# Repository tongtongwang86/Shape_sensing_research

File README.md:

# Capacitive 6DOF Strain Sensor for Soft Robot Shape Reconstruction

This project implements a model-based proprioception system for soft robots using embedded capacitive strain sensors, inspired by the Flex-2P6D sensor design from Feliu-Talegon et al. ("Advancing Soft Robot Proprioception Through 6D Strain Sensors Embedding", Soft Robotics 2025). The approach uses a two-plate capacitive sensor that measures relative displacement and rotation between plates to compute the full 6D strain (twist, bending in two axes, axial stretch, and shear in two axes) at discrete points along the robot body. These strain measurements are then integrated using the Geometric Variable-Strain (GVS) model based on SE(3) Lie group kinematics to reconstruct the complete 3D shape of the soft manipulator. This repository contains the KiCad PCB design files for the sensor board (featuring the AD7147 capacitance-to-digital converter) and a simulation suite that generates synthetic strain data and visualizes the resulting 3D shape reconstruction in MATLAB.

## Initial "Simulation" Results

## PCB Design

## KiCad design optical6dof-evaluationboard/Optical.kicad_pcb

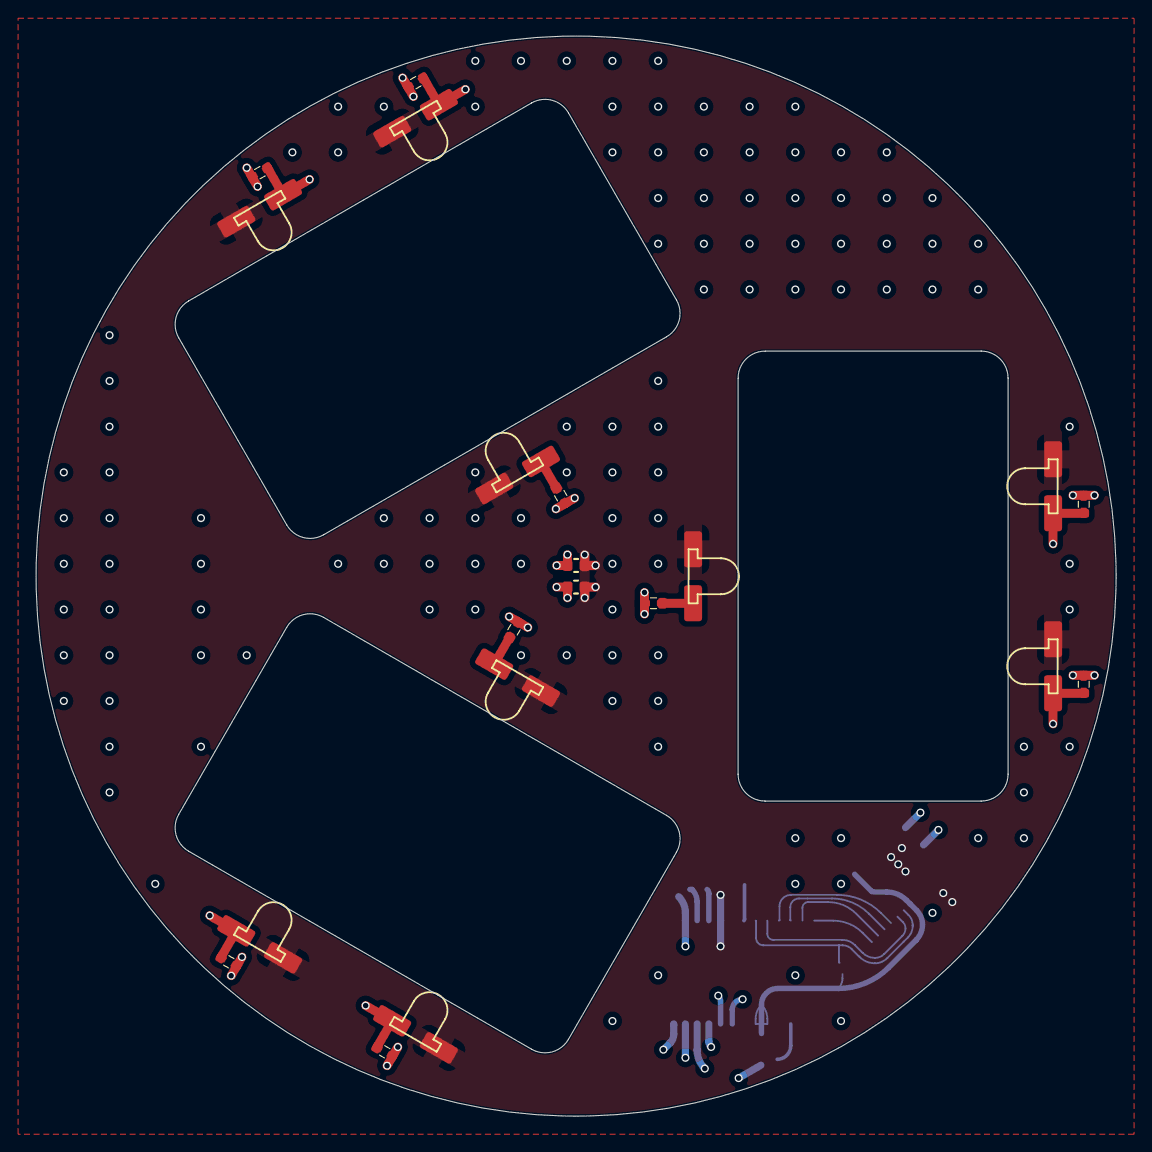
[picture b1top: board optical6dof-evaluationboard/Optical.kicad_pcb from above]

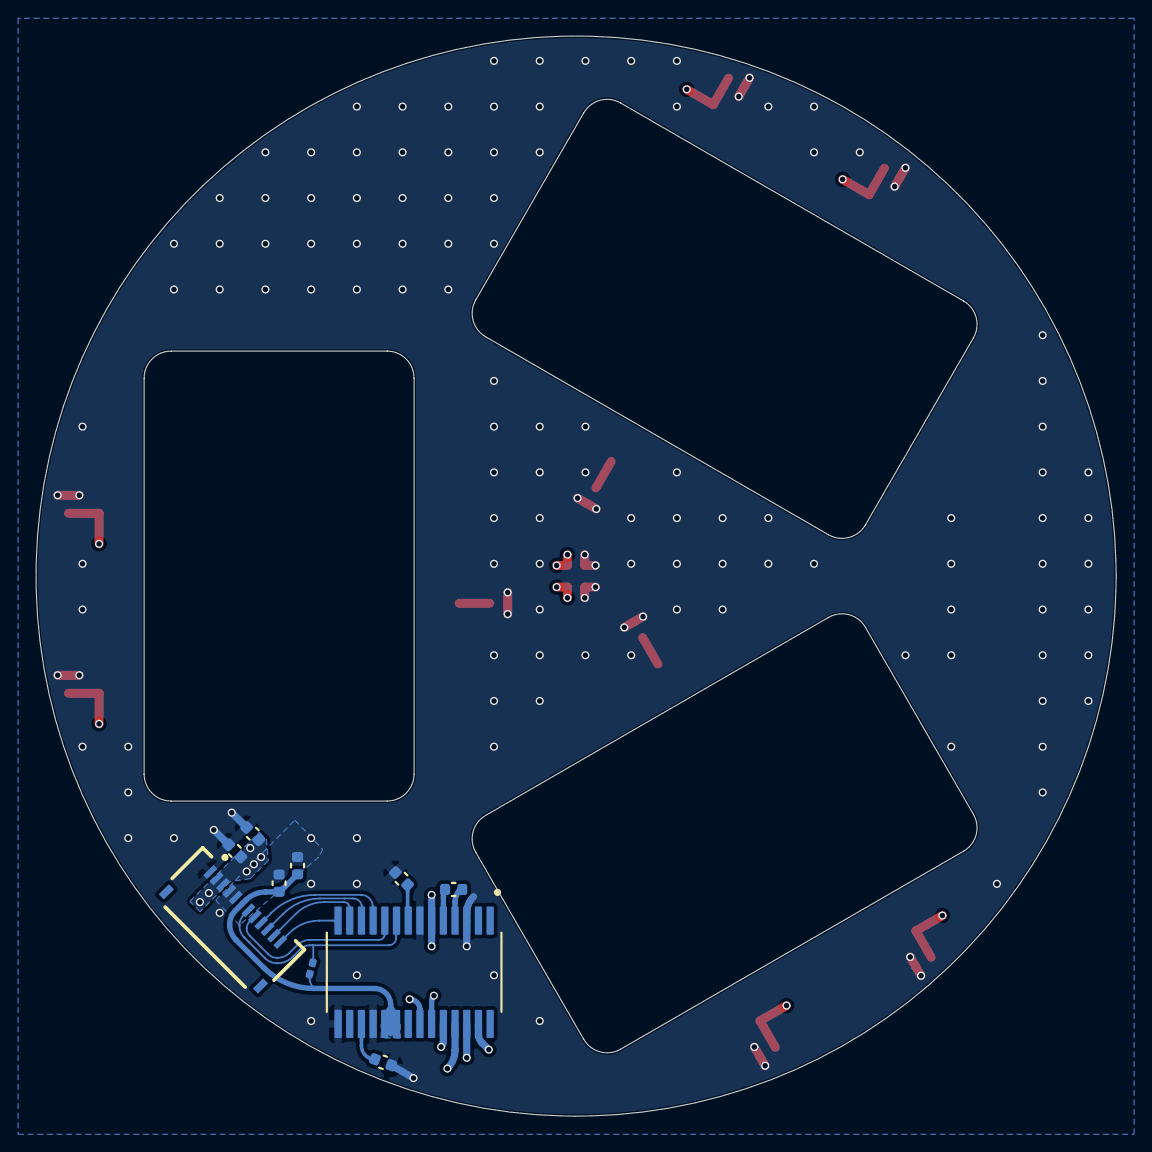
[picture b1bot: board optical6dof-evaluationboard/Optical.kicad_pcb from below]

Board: 4 copper layers, 60.0 x 60.0 mm, 30 parts (10 on the bottom side), 22 nets.

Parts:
C1, C5, C8: 100uF; C_0402_1005Metric
C2, C4: 1uF; C_0402_1005Metric
C3: 4.7nF; C_0402_1005Metric
C6, C7, C9: 10uF; C_0402_1005Metric
D1, D2, D3: LED; APDA3020P3C-P22
J1: FFC2B28-12-G; GCT_FFC2B28-12-G
Q1, Q2, Q3, Q4, Q5, Q6: APDA3020P3C-P22
R1, R2, R4, R5, R6, R7: 2.2K; 0402
R3: 2.2K; R_0201_0603Metric
R8, R9, R10: 220r; 0402
U1: ADS1262IPWR; SOP65P640X120-28N

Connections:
/A1: Q1.2 (E), R1.1, U1.26 (AIN5)
/A2: Q2.2 (E), R2.1, U1.25 (AIN4)
/B1: Q3.2 (E), R4.1, U1.27 (AIN6)
/B2: Q4.2 (E), R5.1, U1.24 (AIN3)
/C1: Q5.2 (E), R6.1, U1.23 (AIN2)
/C2: Q6.2 (E), R7.1, U1.22 (AIN1)
CS: J1.8, U1.10 (CS)
DataReady: J1.12, U1.14 (DRDY)
GND: C1.1, C2.1, C4.1, C5.1, C6.1, C7.1, C8.1, C9.1, J1.1, J1.4, J1.5, R1.2, R2.2, R4.2, R5.2, R6.2, R7.2, R8.2, R9.2, R10.2, U1.3 (AINCOM), U1.7 (AVSS), U1.15 (XTAL1/CLKIN), U1.18 (DGND)
MISO: J1.11, U1.13 (DOUT/DRDY)
MOSI: J1.10, U1.12 (DIN)
unnamed: D1.1 (K), R8.1
unnamed: D2.1 (K), R9.1
unnamed: D3.1 (K), R10.1
unnamed: C2.2, U1.17 (BYPASS)
unnamed: C3.2, U1.5 (CAPN)
unnamed: C3.1, U1.4 (CAPP)
unnamed: C4.2, U1.8 (REFOUT)
SCLK: J1.9, U1.11 (SCLK)
START: J1.7, R3.1, U1.9 (START)
VDD: C1.2, C5.2, C6.2, C7.2, D1.2 (A), D2.2 (A), D3.2 (A), J1.2, J1.3, Q1.1 (C), Q2.1 (C), Q3.1 (C), Q4.1 (C), Q5.1 (C), Q6.1 (C), U1.6 (AVDD)
VDD_digital: C8.2, C9.2, J1.6, R3.2, U1.19 (DVDD), U1.20 (RESET/PWDN)

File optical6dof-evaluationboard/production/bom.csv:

Designator,Footprint,Quantity,Value,LCSC Part #
"C1, C5, C8",0402,3,100uF,
"C2, C4",0402,2,1uF,
C3,0402,1,4.7nF,
"C6, C7, C9",0402,3,10uF,
"D1, D2, D3",APDA3020P3C-P22,3,LED,
J1,GCT_FFC2B28-12-G,1,FFC2B28-12-G,
"Q1, Q2, Q3, Q4, Q5, Q6",APDA3020P3C-P22,6,APDA3020P3C-P22,
"R1, R2, R4, R5, R6, R7",0402,6,2.2K,
"R10, R8, R9",0402,3,220r,
R3,0201,1,2.2K,
U1,SOP65P640X120-28N,1,ADS1262IPWR,

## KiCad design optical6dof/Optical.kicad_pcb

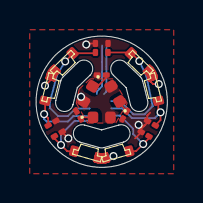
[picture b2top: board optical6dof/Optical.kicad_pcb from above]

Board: 4 copper layers, 7.3 x 7.3 mm, 16 parts (1 on the bottom side), 11 nets.

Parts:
D1, D2, D3: LED; LED_0402_1005Metric
Q1, Q2, Q3: 0603_sidemount
R1, R2, R3, R4, R5, R6: 1.5k; R_01005_0402Metric
R7, R8, R9: 200r; R_01005_0402Metric
U1: MAX11617EWE+T; 21-0491G_W162E2-1_MXM

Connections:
/A1: Q1.2 (E), R1.1, U1.A1 (AIN0)
/A2: Q1.3 (E), R2.1, U1.B1 (AIN9)
/B1: Q2.2 (E), R3.1, U1.A4 (AIN3)
/B2: Q2.3 (E), R4.1, U1.A2 (AIN1)
/C1: Q3.2 (E), R5.1, U1.C4 (AIN5)
/C2: Q3.3 (E), R6.1, U1.B4 (AIN4)
GND: R1.2, R2.2, R3.2, R4.2, R5.2, R6.2, R7.2, R8.2, R9.2, U1.D1 (GND)
unnamed: D1.1 (K), R7.1
unnamed: D2.1 (K), R8.1
unnamed: D3.1 (K), R9.1
VDD: D1.2 (A), D2.2 (A), D3.2 (A), Q1.1 (C), Q2.1 (C), Q3.1 (C), U1.C1 (VDD)

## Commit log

2026-02-24 Initial commit for combined repository
2026-02-24 merged repos
2026-02-24 removed all .DS_Store
2026-02-24 added git ignore
2026-02-24 organized the paths up
2026-02-24 routed the pcb
2026-02-24 layout changes to schematic
2026-02-24 sum math
2026-02-25 basic simulations involving the light hitting the transistors
2026-02-25 latex justification
2026-04-19 test design, and datasheets
2026-05-25 new pcb
2026-05-25 random stuff to push
